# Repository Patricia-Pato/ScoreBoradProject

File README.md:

# ScoreBorad_Project
 2020年度 情報工学科課題研究 体育祭用得点掲示板の製作
 
# 概要
体育祭での得点表示を行うためのLED得点表示板を課題研究にて製作することになった。
目的としてはもともと得点掲示板を管理運用していた電子工作同好会の部員はもちろんそれ以外の人でも問題なく運用できるレベルで
その後の管理等を可能な限り容易にすることを目標としている。
この課題研究で作製するのはもちろん得点掲示板本体であるが、それらに関するマニュアルや資料、設計図、プログラムなど
使用した全てのものを記録に残して行くことも目標である。

# 理論
詳しくは[理論](./THEORY.md)を参照

# 歴史
元々は総合電気科の課題研究で製作されたものだった、その当時は人ブロックの得点のみを表示していた。
その課題研究の発表会で以降の改良は電子工作同好会が受け継いだ。
その後、電子工作同好会で何代かの進化を経て私の課題研究に続いている。
1度体育祭に使用してからというもの毎年使用する流れとなり問題、課題はありながらどうにか運用しているが
流石にダラダラと続きすぎてある。

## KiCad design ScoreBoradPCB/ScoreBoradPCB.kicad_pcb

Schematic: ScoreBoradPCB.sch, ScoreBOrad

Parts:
C1, C2, C4, C6: 0.1u; C_0603_1608Metric
C3, C5, C7: 10u; C_0603_1608Metric
D1, D2, D3, D4, D5, D6: GS1010FL; D_SOD-123F
D7, D8, D9, D10: LED; LED_0603_1608Metric
DS1: 2831BS-RIGHT-ANGLE; DIPS762W45P254L2253H610Q12N; Manufacturer_Part_Number 2831BS-RIGHT-ANGLE
J1, J2, J3: Conn_01x08_Male; JST_VH_B8P-VH_1x08_P3.96mm_Vertical
J4, J5: Conn_01x04_Male; JST_VH_B4P-VH_1x04_P3.96mm_Vertical
J6, J7: Conn_01x02_Male; JST_XH_B2B-XH-A_1x02_P2.50mm_Vertical
J8: Conn_01x06_Male; PinHeader_1x06_P2.54mm_Horizontal
J9, J10: Conn_01x02_Male; PinHeader_1x02_P2.54mm_Vertical
Q1, Q3, Q5, Q7, Q9, Q11, Q13, Q17, Q20, Q23, Q24: 2N7002K; SOT-23
Q2, Q4, Q6, Q8, Q10, Q12, Q14, Q16, Q19, Q22: NP52N06SLG; TO-252-3_TabPin4
Q15, Q18, Q21: BSS84; SOT-23
R1, R4, R7, R10, R13, R16, R19, R25, R26, R32, R33, R39, R40: 100; R_0603_1608Metric
R2, R3, R5, R6, R8, R9, R11, R12, R14, R15, R17, R18, R20, R21, R22, R24, R27, R28, R29, R31, R34, R35, R36, R38, R41, R42, R58, R59, R62, R63: 15k; R_0603_1608Metric
R23, R30, R37, R46, R47, R48, R49, R51, R52, R53, R54, R55, R56, R57: 300; R_0603_1608Metric
R43, R44, R45, R60, R61: 1k; R_0603_1608Metric
SW1, SW2, SW3, SW4, SW5, SW6, SW7: SW_Push; SW_PUSH_6mm_H5mm
U1: PIC16F1938; DIP-28_W7.62mm_Socket
U2, U4, U6: TLP291; SOIC-4_4.55x2.6mm_P1.27mm
U3, U5, U7: IR2104; SOIC-8_3.9x4.9mm_P1.27mm

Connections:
+5V: C1.1, J4.2, J5.2, J8.5, J9.1, J10.1, Q15.2, Q18.2, Q21.2, R22.1, R29.1, R36.1, R48.1, R60.1, R61.1, U1.20 (VDD)
+12V: C2.1, C4.1, C6.1, D2.2, D4.2, D6.2, J4.3, J5.3, R3.1, R6.1, R9.1, R12.1, R15.1, R18.1, R21.1, R46.1, R63.2, U2.4, U3.1, U4.4, U5.1, U6.4, U7.1
+48V: J4.1, J5.1, Q16.4, Q19.4, Q22.4, R43.1
/Address_1: J9.2, R58.1, U1.16 (RC5)
/Address_2: J10.2, R59.1, U1.17 (RC6)
/Anode_hun: C7.2, J3.1, Q22.3, Q23.3, R41.1, U7.6
/Anode_one: C3.2, J1.1, Q16.3, Q17.3, R27.1, U3.6
/Anode_ten: C5.2, J2.1, Q19.3, Q20.3, R34.1, U5.6
/Cathode_a: J1.2, J2.2, J3.2, Q2.4, R57.2
/Cathode_b: J1.3, J2.3, J3.3, Q4.4, R55.2
/Cathode_c: J1.4, J2.4, J3.4, Q6.4, R53.2
/Cathode_d: J1.5, J2.5, J3.5, Q8.4, R52.2
/Cathode_e: J1.6, J2.6, J3.6, Q10.4, R51.2
/Cathode_f: J1.7, J2.7, J3.7, Q12.4, R56.2
/Cathode_g: J1.8, J2.8, J3.8, Q14.4, R54.2
/Dig_hun: D5.1, DS1.12
/Dig_one: D1.1, DS1.8
/Dig_ten: D3.1, DS1.9
/ICSP_CLK: J8.2, U1.27 (RB6)
/ICSP_DAT: J8.3, U1.28 (RB7)
/Minus_hun: SW1.2, U1.26 (RB5)
/Minus_one: SW5.2, U1.22 (RB1)
/Minus_ten: SW3.2, U1.24 (RB3)
/Place_hun: Q21.1, R36.2, U1.13 (RC2)
/Place_one: Q15.1, R22.2, U1.11 (RC0)
/Place_ten: Q18.1, R29.2, U1.12 (RC1)
/Plus_hun: SW2.2, U1.25 (RB4)
/Plus_one: SW6.2, U1.21 (RB0)
/Plus_ten: SW4.2, U1.23 (RB2)
/SCL: J6.2, J7.2, R61.2, U1.14 (RC3)
/SDA: J6.1, J7.1, R60.2, U1.15 (RC4)
/Segment_a: R1.2, U1.2 (RA0)
/Segment_b: R4.2, U1.3 (RA1)
/Segment_c: R7.2, U1.4 (RA2)
/Segment_d: R10.2, U1.5 (RA3)
/Segment_e: R13.2, U1.6 (RA4)
/Segment_f: R16.2, U1.7 (RA5)
/Segment_g: R19.2, U1.10 (RA6)
/ShutDown: Q24.1, R49.1, R62.1, U1.9 (RA7)
/Vpp_MCLR: J8.6, SW7.2, U1.1 (VPP/~MCLR/RE3)
GND: C1.2, C2.2, C4.2, C6.2, D7.1, D8.1, D9.1, D10.1, J4.4, J5.4, J8.4, Q1.2, Q2.3, Q3.2, Q4.3, Q5.2, Q6.3, Q7.2, Q8.3, Q9.2, Q10.3, Q11.2, Q12.3, Q13.2, Q14.3, Q17.2, Q20.2, Q23.2, Q24.2, R2.1, R5.1, R8.1, R11.1, R14.1, R17.1, R20.1, R24.2, R28.1, R31.2, R35.1, R38.2, R42.1, R58.2, R59.2, R62.2, SW1.1, SW2.1, SW3.1, SW4.1, SW5.1, SW6.1, SW7.1, U1.8 (VSS), U1.19 (VSS), U2.2, U3.4, U4.2, U5.4, U6.2, U7.4
unnamed: C3.1, D2.1, U3.8
unnamed: C5.1, D4.1, U5.8
unnamed: C7.1, D6.1, U7.8
unnamed: D1.2, Q15.3, R23.2
unnamed: D3.2, Q18.3, R30.2
unnamed: D5.2, Q21.3, R37.2
unnamed: D7.2, R45.2
unnamed: D8.2, R47.2
unnamed: D9.2, R48.2
unnamed: D10.2, R49.2
unnamed: DS1.1, R51.1
unnamed: DS1.2, R52.1
unnamed: DS1.4, R53.1
unnamed: DS1.5, R54.1
unnamed: DS1.7, R55.1
unnamed: DS1.10, R56.1
unnamed: DS1.11, R57.1
unnamed: Q1.1, R1.1, R2.2
unnamed: Q1.3, Q2.1, R3.2
unnamed: Q3.1, R4.1, R5.2
unnamed: Q3.3, Q4.1, R6.2
unnamed: Q5.1, R7.1, R8.2
unnamed: Q5.3, Q6.1, R9.2
unnamed: Q7.1, R10.1, R11.2
unnamed: Q7.3, Q8.1, R12.2
unnamed: Q9.1, R13.1, R14.2
unnamed: Q9.3, Q10.1, R15.2
unnamed: Q11.1, R16.1, R17.2
unnamed: Q11.3, Q12.1, R18.2
unnamed: Q13.1, R19.1, R20.2
unnamed: Q13.3, Q14.1, R21.2
unnamed: Q16.1, R25.1, R27.2
unnamed: Q17.1, R26.1, R28.2
unnamed: Q19.1, R32.1, R34.2
unnamed: Q20.1, R33.1, R35.2
unnamed: Q22.1, R39.1, R41.2
unnamed: Q23.1, R40.1, R42.2
unnamed: Q24.3, R63.1, U3.3, U5.3, U7.3
unnamed: R23.1, U2.1
unnamed: R24.1, U2.3, U3.2
unnamed: R25.2, U3.7
unnamed: R26.2, U3.5
unnamed: R30.1, U4.1
unnamed: R31.1, U4.3, U5.2
unnamed: R32.2, U5.7
unnamed: R33.2, U5.5
unnamed: R37.1, U6.1
unnamed: R38.1, U6.3, U7.2
unnamed: R39.2, U7.7
unnamed: R40.2, U7.5
unnamed: R43.2, R44.1
unnamed: R44.2, R45.1
unnamed: R46.2, R47.1

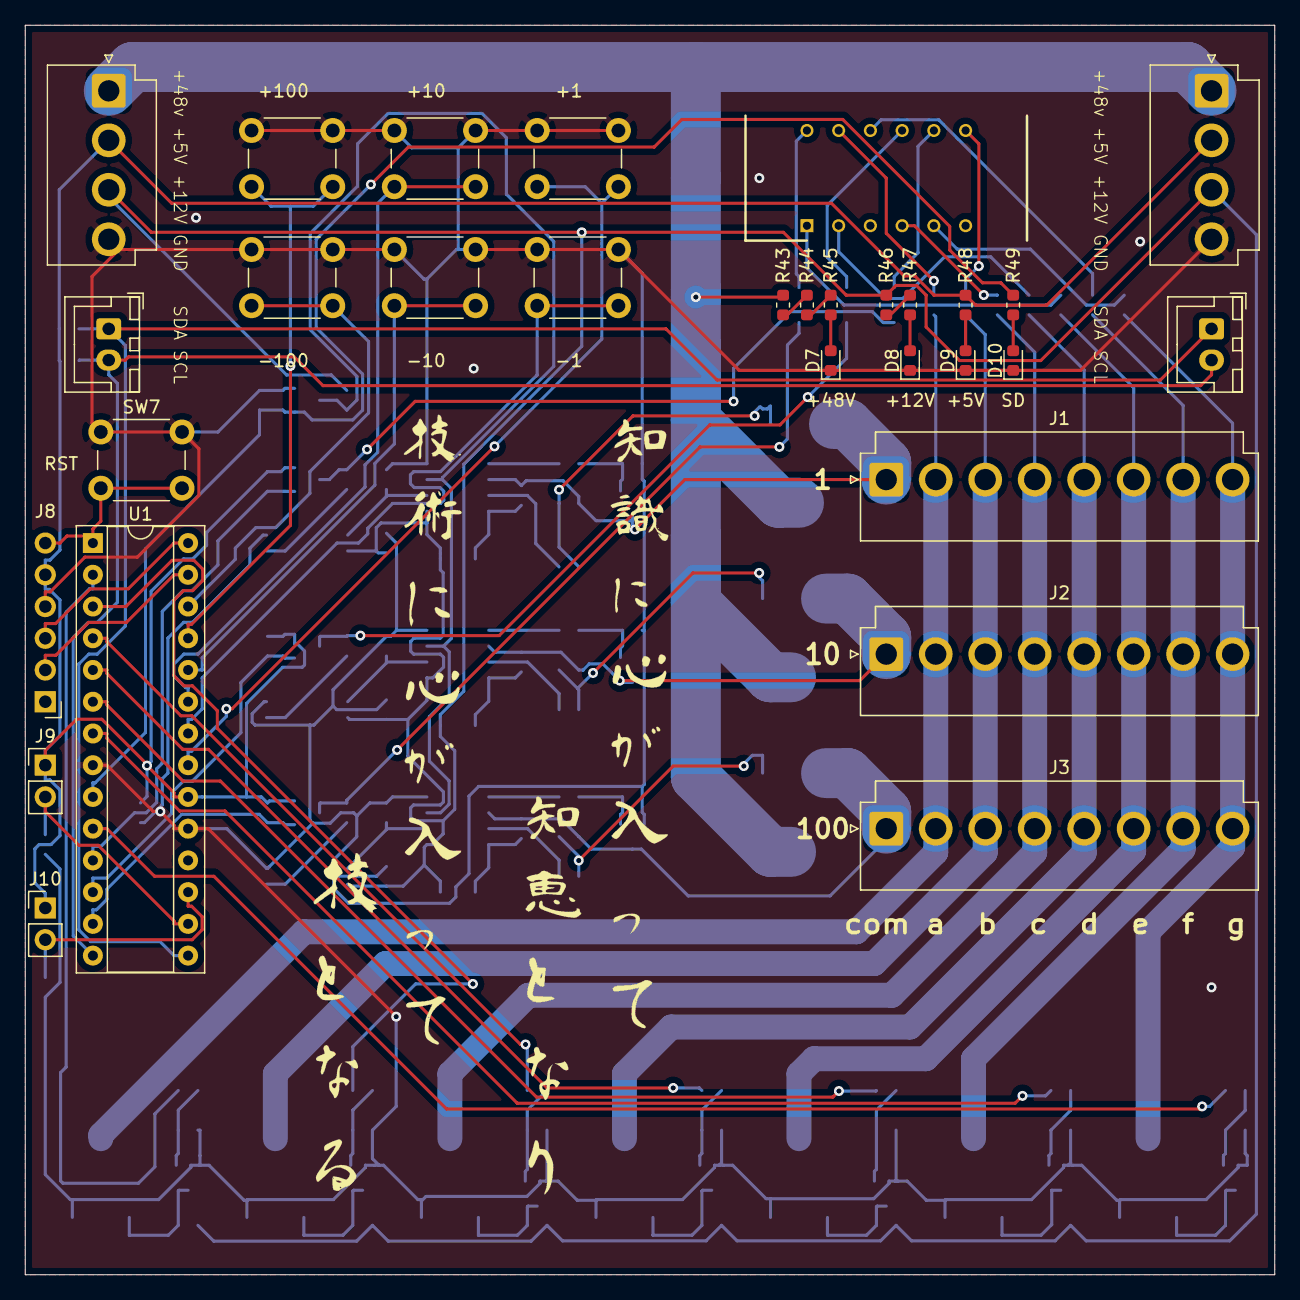
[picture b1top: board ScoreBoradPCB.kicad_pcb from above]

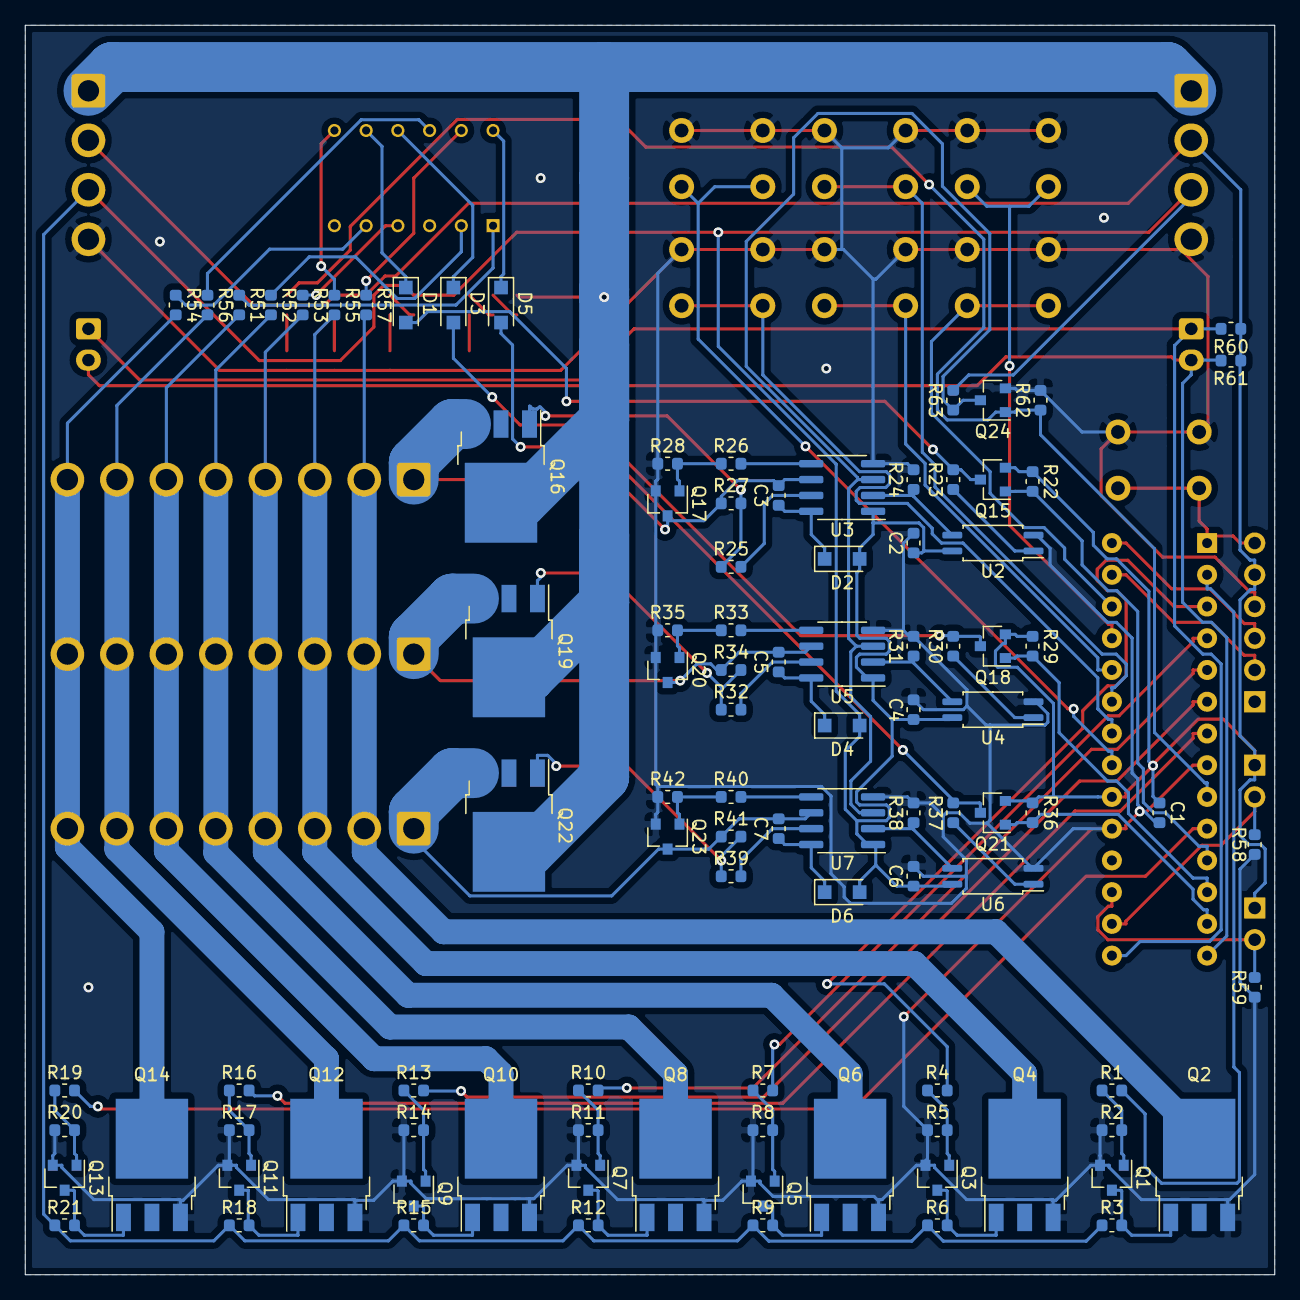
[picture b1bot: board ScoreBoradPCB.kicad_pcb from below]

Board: 2 copper layers, 100.0 x 100.0 mm, 128 parts (98 on the bottom side), 94 nets.

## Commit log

2020-09-05 既存ファイルの追加
2020-09-06 フットプリント配置完了
2020-09-06 基板完成
2020-09-06 twe-liteテストコード
2020-09-06 校訓追加
2020-09-07 パターン完成
2020-09-09 通信基板回路完成
2020-09-09 通信基板パターン化完成
2020-09-10 ガーバーファイル出力
2020-09-20 ゲート抵抗を削除
2020-09-23 トワイライト受信側プログラム変更
2020-11-07 コンソールアプリ作成
2020-11-17 ScoreBorad2の追加
2020-12-12 点数ロール機能追加
2020-12-12 twe-lite回転コントールプログラム一部完成
    制御基板側での点数更新がtweliteに反映されないので点数が勝手に変わります。
    PICからtwe-lliteにi2cで送り返す必要あり
2020-12-12 相互通信
2021-01-02 時刻送信
2021-01-14 リハーサル用
2021-01-14 SWノイズ対策
2021-01-19 在庫リスト更新
2021-01-23 回路修正
